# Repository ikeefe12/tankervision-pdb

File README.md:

# TankerVision Power Distribution Board

A four-layer KiCad power distribution board (PDB) for the TankerVision robot. It
accepts USB-C PD or an 18.5–20 V DC barrel-jack input, maintains a
supercapacitor-backed rail so an onboard NVIDIA Jetson can shut down cleanly after
input loss, and exposes four independently protected, firmware-controlled output
ports.

Designed in KiCad 9.0.7. Revision 1.0 was fabricated and assembled by JLCPCB in
August 2026.

| | |
|---|---|
|  |  |

## Highlights

- **Dual redundant input** — USB-C PD (CYPD3177 requesting 20 V) and a DC barrel
  jack are ORed through two reverse-blocking LM73100 ideal-diode switches.
- **Supercapacitor backup** — a BQ24640 charges an external bank through a 24.5 V
  LM5155 boost; a TPS2121 priority mux transfers the backed `+VBUS_SS` domain to the
  bank in roughly 5 µs when the input rail collapses.
- **Orderly shutdown** — the backed rails feed the ESP32-S3, which sheds loads,
  pulses the Jetson power button, and watches stored energy on the supercap ADC
  divider to decide when to commit to shutdown.
- **Firmware-independent boot** — input switch → mux IN1 → `+VBUS_SS` → 5 V buck →
  3.3 V LDO brings up the ESP32-S3 with no firmware involvement; every other load
  rail is deliberately under software control.
- **Protected outputs** — four LM73100 output switches provide inrush control,
  reverse blocking, power-good, and current monitoring per port.
- **Full supervision** — fourteen TLV7031 comparators condition status signals and
  two TCA9535 I²C expanders carry enables and status back to the ESP32-S3.

## Board summary

| Item | Value |
|---|---|
| Outline | 100 mm × 100 mm |
| Stackup | 4-layer, 1.6 mm FR-4, 35 µm (1 oz) copper on all layers |
| Planes | In1.Cu solid GND; In2.Cu predominantly GND with selected routing |
| References | 452 in schematic and PCB, matched one-to-one |
| Production BOM | 444 fitted references in 84 orderable groups |
| Input | USB-C PD, or 18.5–20 V DC barrel jack |
| Outputs | 4 protected ports (`+VBUS`, `+5V_VBUS`, `+VBUS_SS`, `+5V_SS`) |
| Controller | ESP32-S3-WROOM-1-N8R8 |

## Documentation

The design is documented per functional block, with schematic labels rather than
drawing coordinates used as the stable way to locate each circuit.

- **[docs/README.md](docs/README.md)** — start here: block index and power-rail table
- **[docs/system-architecture.md](docs/system-architecture.md)** — power flow, control
  and status map, ESP32 pin map, sequencing
- **[docs/pcb-layout.md](docs/pcb-layout.md)** — layout review, stackup, routing,
  fabrication decisions, revision-1.0 order record
- **[docs/issues.md](docs/issues.md)** — open design concerns and pre-deployment
  bench checks
- **[docs/blocks/](docs/blocks/)** — sixteen per-block documents covering USB-PD,
  inrush control, the power mux, the supercap charger and switch, the boost and
  bucks, LDOs, output switches, the ESP32, I/O expanders, comparators, analog
  switches, the Jetson power button, and ADC monitoring

Firmware and board verification:

- **[firmware/deployment/README.md](firmware/deployment/README.md)** — automatic
  startup, supercap maintenance charging, 1 Hz USB telemetry and fixed 60-second
  Jetson shutdown/reboot sequence
- **[firmware/deployment/API.md](firmware/deployment/API.md)** — Jetson USB API,
  with a [Python reference client](firmware/deployment/jetson/README.md)
- **[firmware/deployment/results/upload-2026-09-16/README.md](firmware/deployment/results/upload-2026-09-16/README.md)**
  — verified deployment upload, charging/PG observations and serial reopen results
- **[firmware/board_control_test/README.md](firmware/board_control_test/README.md)**
  — reusable board drivers, bench procedures and historical test results

Generated exports for quick reading without KiCad:

- [docs/exports/tankervision-pdb-schematic.pdf](docs/exports/tankervision-pdb-schematic.pdf)
- [docs/exports/tankervision-pdb-bom.csv](docs/exports/tankervision-pdb-bom.csv)

## Repository layout

```text
hardware/tankervision-pdb/   KiCad project (schematic, PCB, project library tables)
libraries/symbols/           custom symbol libraries (.kicad_sym)
libraries/footprints/        custom footprint libraries (.pretty)
libraries/3dmodels/          custom 3D models referenced by those footprints
docs/                        design documentation, generated exports and renders
firmware/deployment/         ESP32 deployment firmware, Jetson API/client and tests
firmware/board_control_test/  hardware bench firmware, procedures and captured results
manufacturing/rev-1_0/       as-ordered JLCPCB fabrication and assembly package
```

## Opening the project

Requires **KiCad 9.0** or newer.

```sh
git clone https://github.com/ikeefe12/tankervision-pdb.git
cd tankervision-pdb
kicad hardware/tankervision-pdb/tankervision-pdb.kicad_pro
```

The project's `sym-lib-table` and `fp-lib-table` resolve every custom library
through `${KIPRJMOD}/../../libraries/...`, so the libraries load from this
repository with no global KiCad configuration. Standard symbols, footprints, and 3D
models come from the stock KiCad libraries installed with KiCad.

## Design state

Revision 1.0 was ordered from JLCPCB on 2026-08-24. The CAD review finds no
remaining electrical schematic blocker. The firmware records now include successful
converter/port control checks, real-bank charging and backup intervals, and the
first deployment upload with 1 Hz telemetry and same-boot serial reopen on the Mac.
The remaining integration checks in [docs/issues.md](docs/issues.md) include loaded
Jetson shutdown and backup endurance, source hot-plug, thermal validation of the
3.3 V LDO, and output-switch overload cases. The recorded unloaded and MCU-only
checks do not establish those loaded behaviors.

Verification on the current sources with KiCad 9.0.7:

- PCB DRC with schematic parity: 0 violations, 0 unconnected pads, 0 footprint
  errors, 0 parity issues.
- ERC is clean in the KiCad GUI with the project's review exclusions applied.
  Command-line ERC does not apply those exclusions and reports six
  `power_pin_not_driven` items, all of which are the reviewed and accepted cases
  described in the block documentation.

## Credit

Designed by Ian Keefe at TRAILab, University of Toronto Institute for Aerospace
Studies.

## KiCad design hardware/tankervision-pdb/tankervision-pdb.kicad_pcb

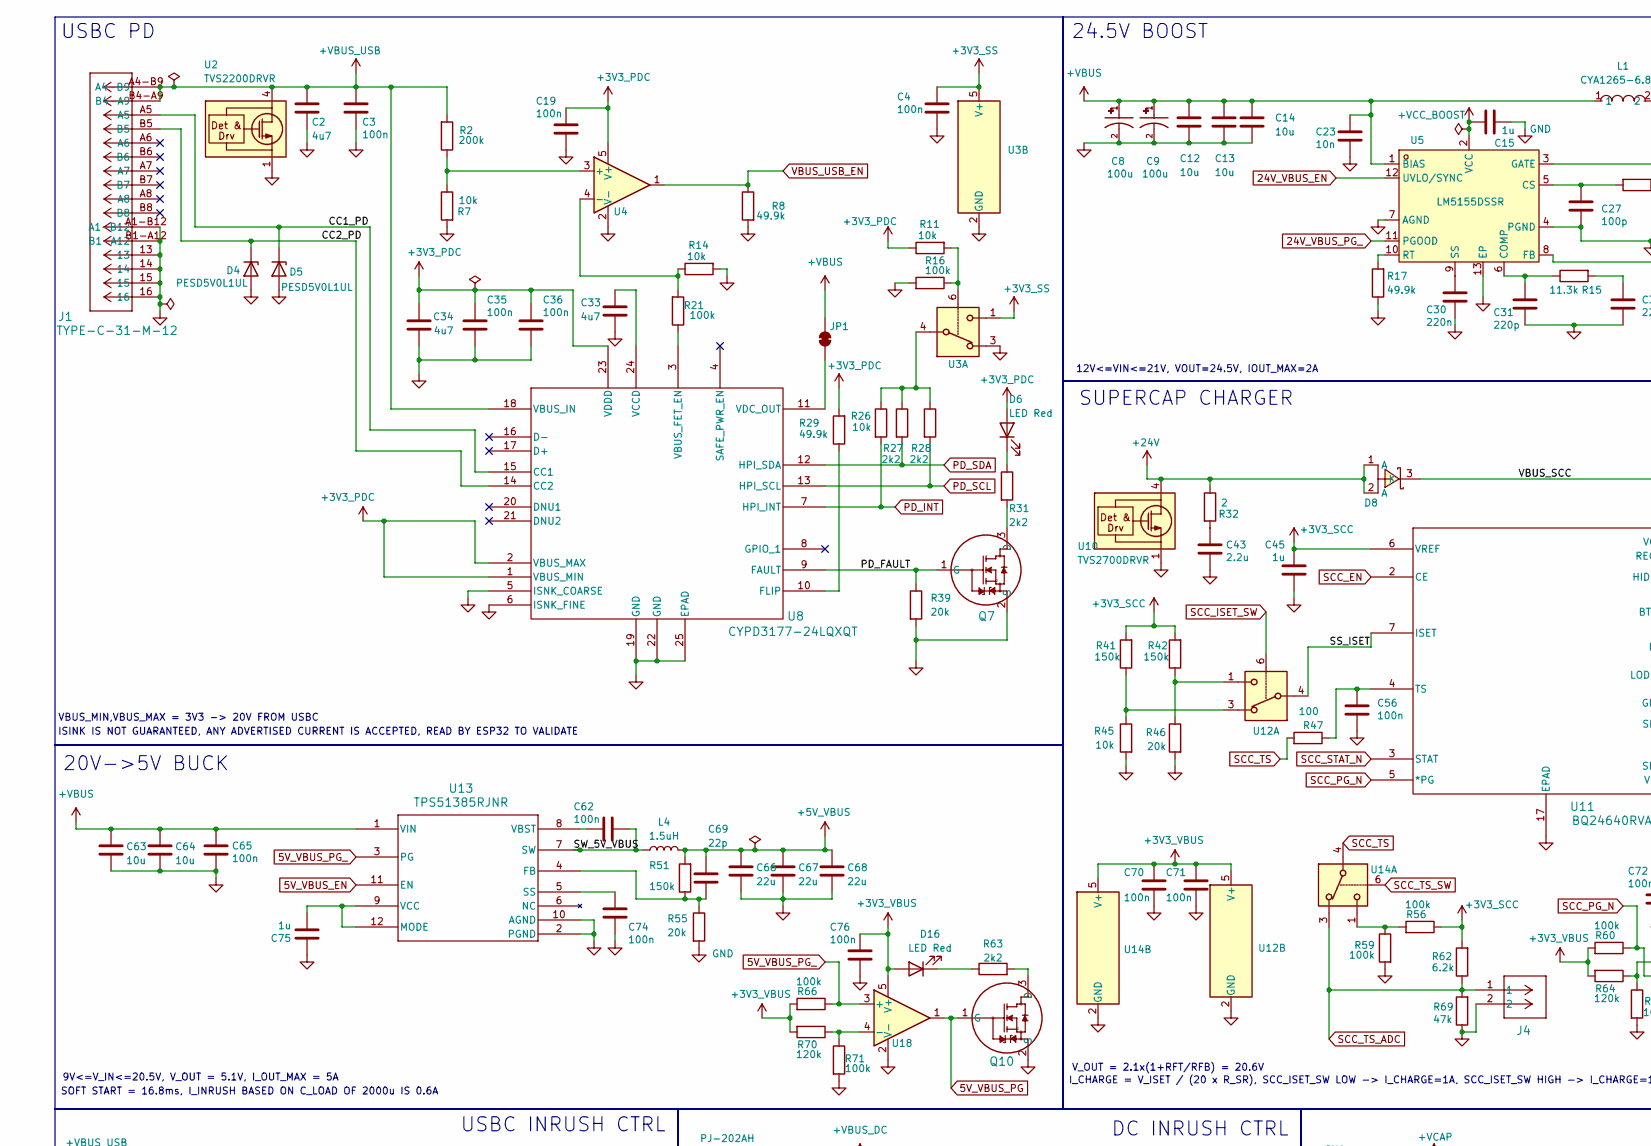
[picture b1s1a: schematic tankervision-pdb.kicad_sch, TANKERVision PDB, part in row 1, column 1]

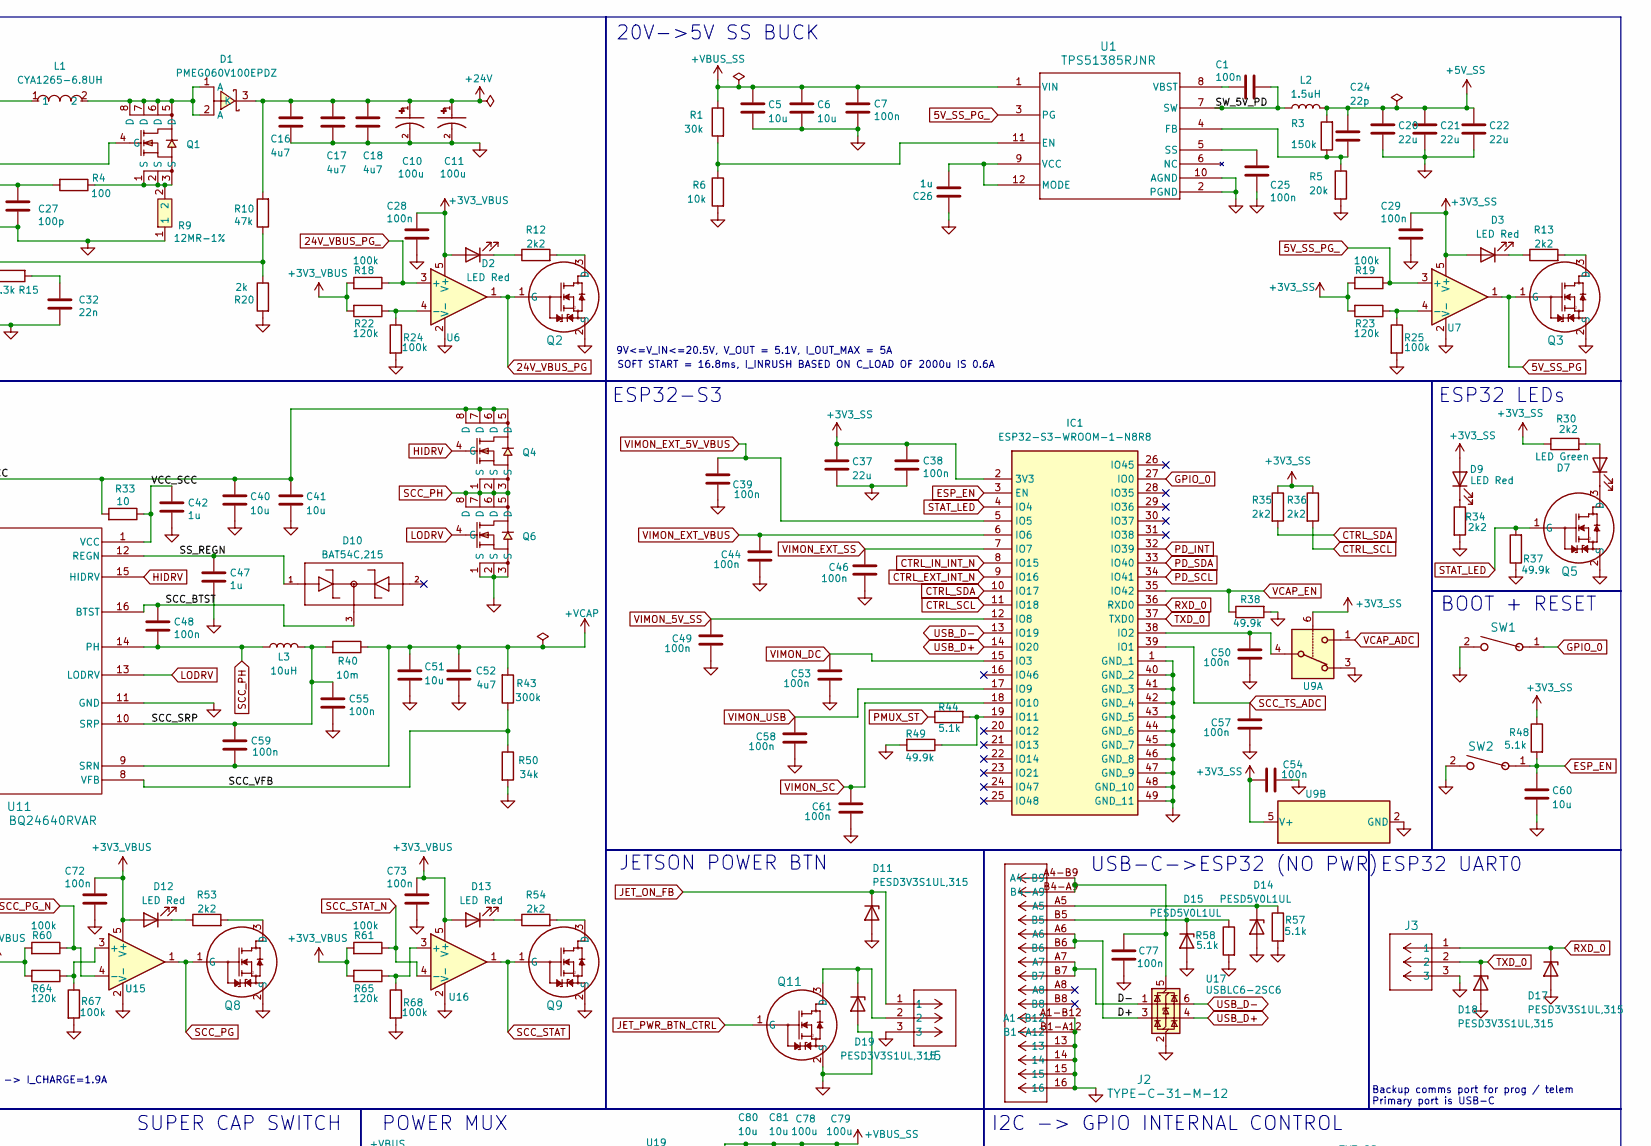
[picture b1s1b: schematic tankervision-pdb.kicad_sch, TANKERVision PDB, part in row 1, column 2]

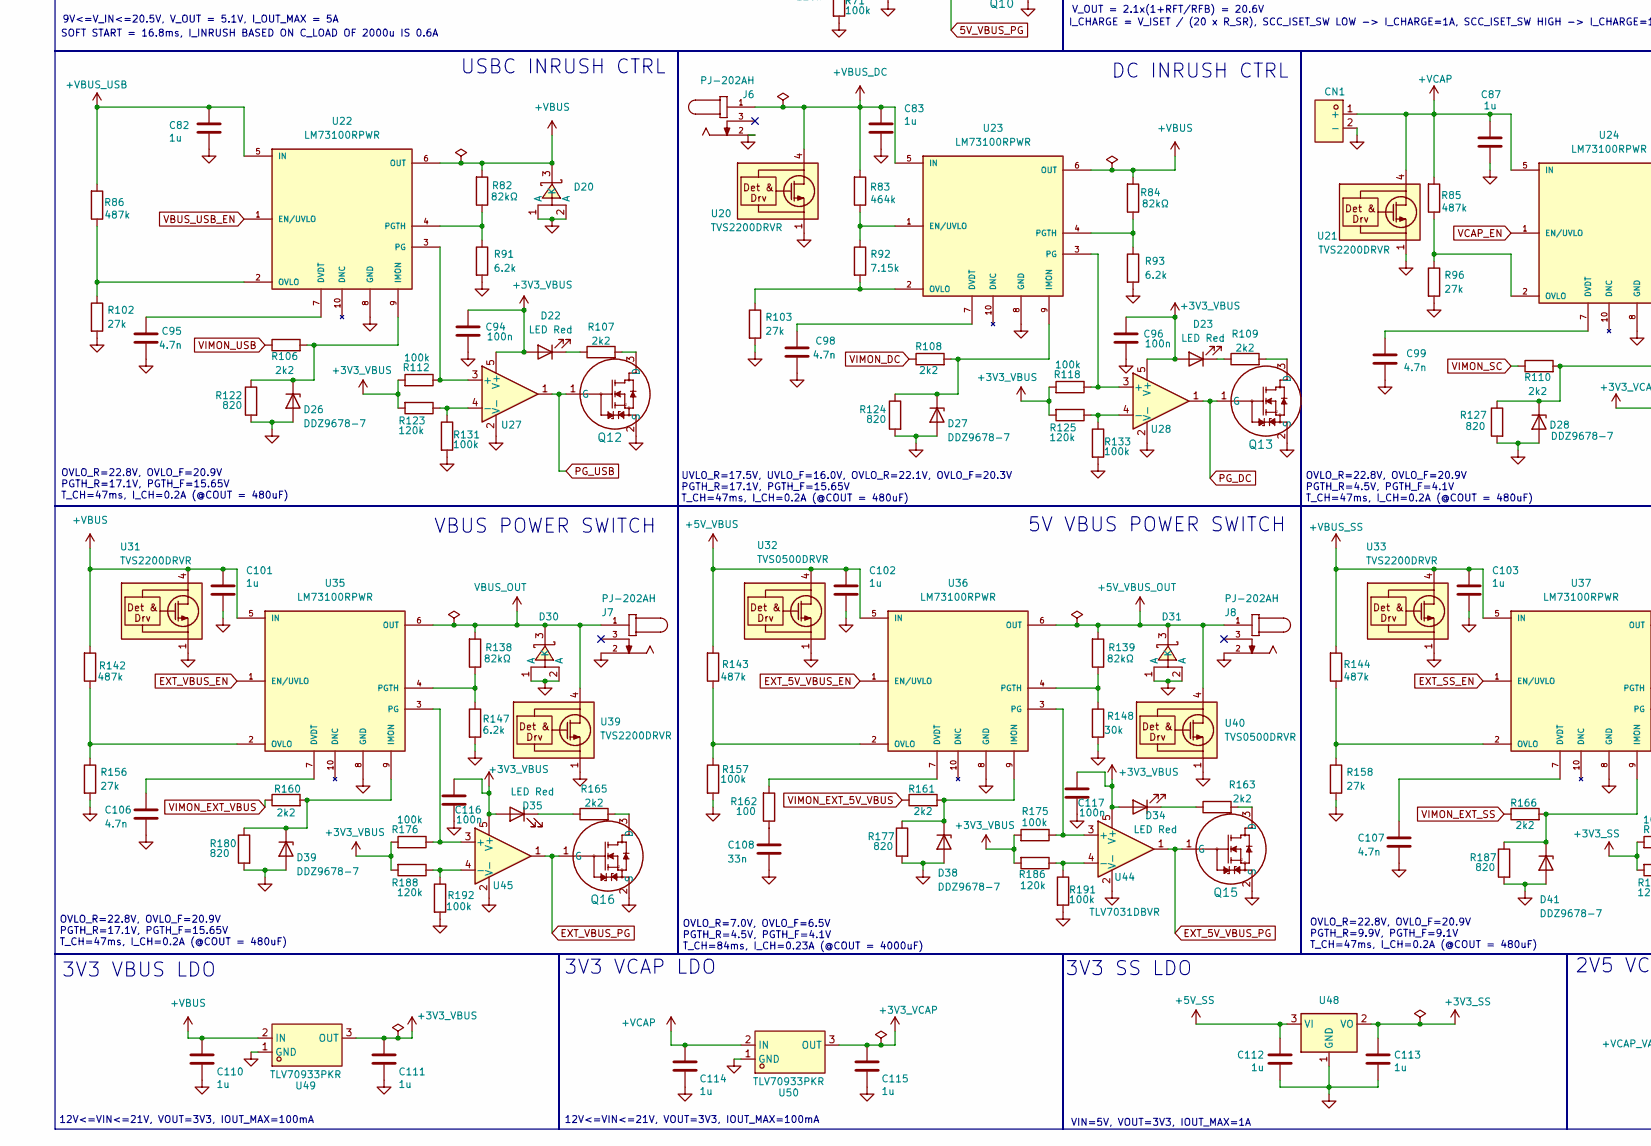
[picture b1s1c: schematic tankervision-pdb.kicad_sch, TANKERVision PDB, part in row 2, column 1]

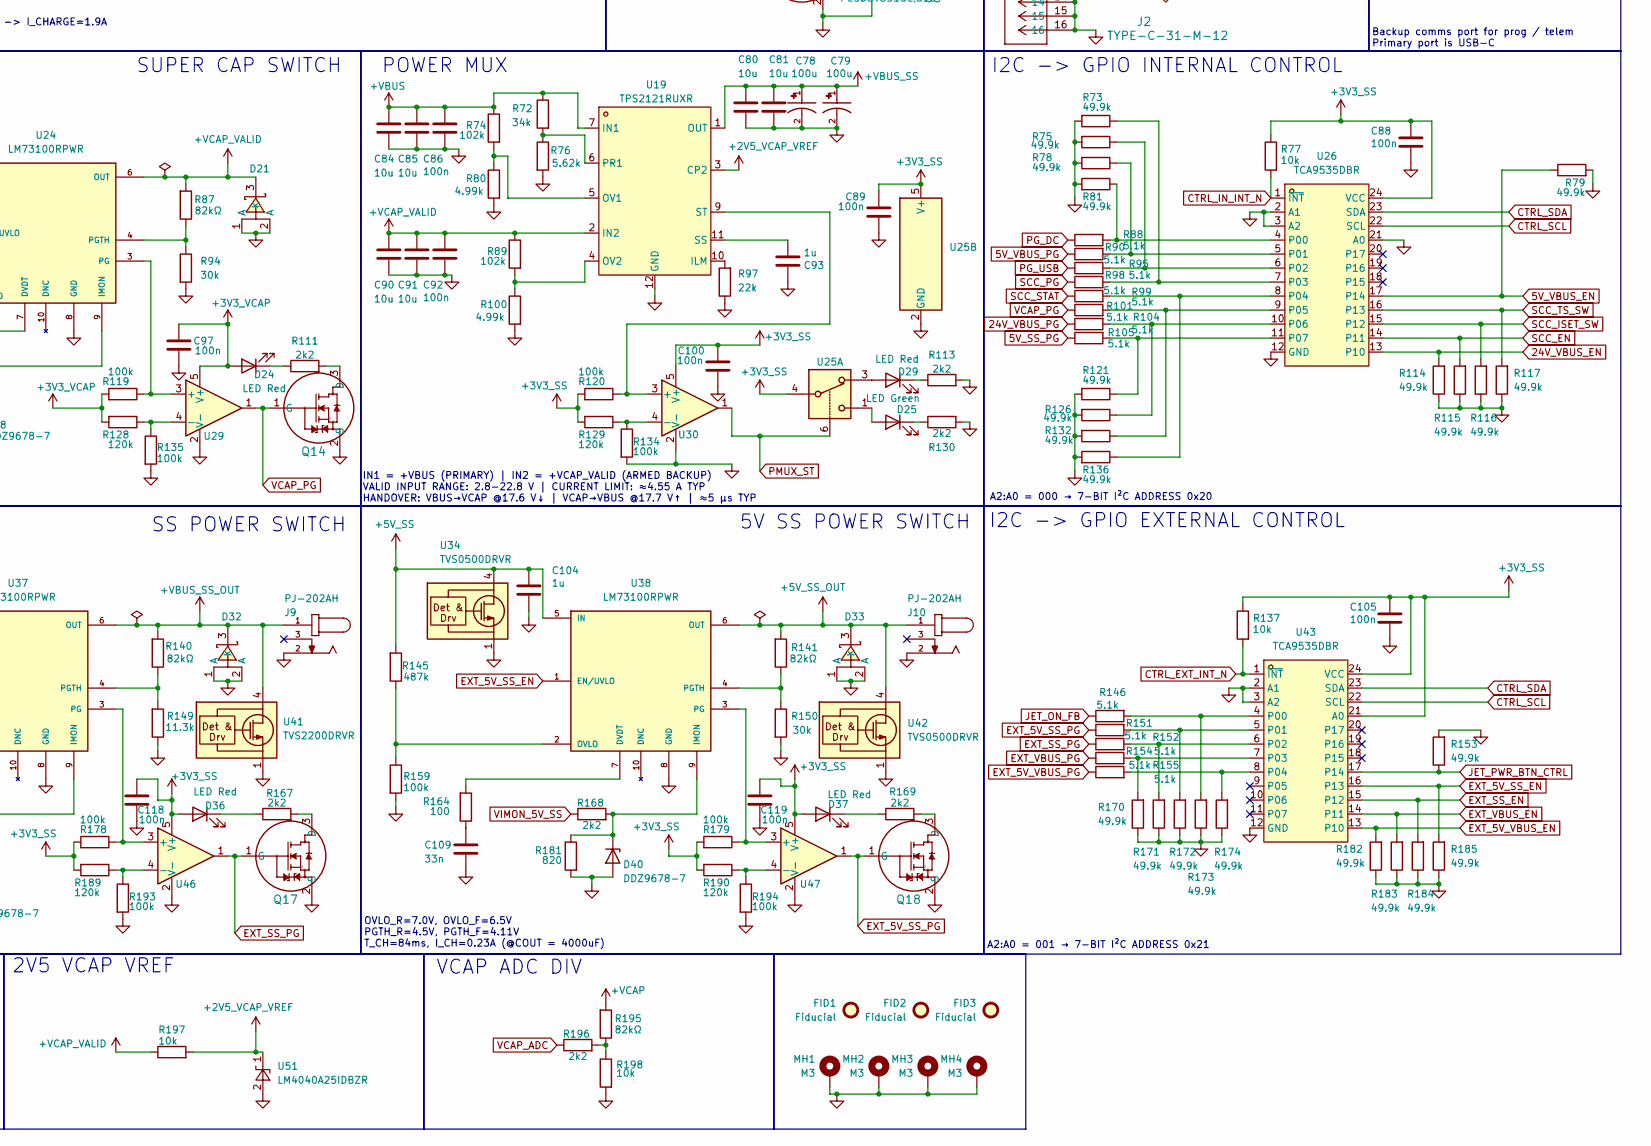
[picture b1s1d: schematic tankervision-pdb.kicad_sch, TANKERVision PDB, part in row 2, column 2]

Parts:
C1, C3, C4, C7, C19, C25, C28, C29, C35, C36, C38, C39, C44, C46, C48, C49, C50, C53, C54, C55, C56, C57, C58, C59, C61, C62, C65, C70, C71, C72, C73, C74, C76, C77, C86, C88, C89, C92, C94, C96, C97, C100, C105, C116, C117, C118, C119: 100n; C_0603_1608Metric; Manufacturer_Part_Number CC0603KRX7R9BB104; JLCPCB Part # C14663
C2, C16, C17, C18, C33, C34, C52: 4u7; C_1206_3216Metric; Manufacturer_Part_Number 1206B475K500NT; JLCPCB Part # C29823
C5, C6, C12, C13, C14, C40, C41, C51, C60, C63, C64, C80, C81, C84, C85, C90, C91: 10u; C_1206_3216Metric; Manufacturer_Part_Number CL31A106KBHNNNE; JLCPCB Part # C13585
C8, C9, C10, C11, C78, C79: 100u; CAP_EEHZA1H101V; Manufacturer_Part_Number EEHZA1H101V; JLCPCB Part # C454363
C15, C26, C42, C45, C47, C75, C82, C83, C87, C93, C101, C102, C103, C104, C110, C111, C112, C113, C114, C115: 1u; C_0805_2012Metric; Manufacturer_Part_Number CL21B105KBFNNNE; JLCPCB Part # C28323
C20, C21, C22, C37, C66, C67, C68: 22u; C_1206_3216Metric; Manufacturer_Part_Number CL31A226KAHNNNE; JLCPCB Part # C12891
C23: 10n; C_0603_1608Metric; Manufacturer_Part_Number 0603B103K500NT; JLCPCB Part # C57112
C24, C69: 22p; C_0603_1608Metric; Manufacturer_Part_Number CL10C220JB8NNNC; JLCPCB Part # C1653
C27: 100p; C_0603_1608Metric; Manufacturer_Part_Number 0603CG101F500NT; JLCPCB Part # C55722
C30: 220n; C_0603_1608Metric; Manufacturer_Part_Number CL10B224KA8NNNC; JLCPCB Part # C21120
C31: 220p; C_0603_1608Metric; Manufacturer_Part_Number GCM1885C2A221JA16D; JLCPCB Part # C388907
C32: 22n; C_0603_1608Metric; Manufacturer_Part_Number CL10B223KB8NNNC; JLCPCB Part # C21122
C43: 2.2u; C_1206_3216Metric; Manufacturer_Part_Number CL31B225KBHNNNE; JLCPCB Part # C50254
C95, C98, C99, C106, C107: 4.7n; C_0805_2012Metric_Pad1.18x1.45mm_HandSolder; Manufacturer_Part_Number 0805B472K500NT; JLCPCB Part # C1744
C108, C109: 33n; C_0805_2012Metric_Pad1.18x1.45mm_HandSolder; Manufacturer_Part_Number 0805B333K500NT; JLCPCB Part # C1739
CN1: XT30APW-M; CONN-TH_XT30APW-M; Manufacturer_Part_Number XT30APW-M; JLCPCB Part # C5818955
D1, D8, D20, D21, D30, D31, D32, D33: PMEG060V100EPDZ; SOT1289_L5.8-W4.4-LS6.5-RD; Manufacturer_Part_Number PMEG060V100EPDZ; JLCPCB Part # C552792
D2, D3, D6, D9, D12, D13, D16, D22, D23, D24, D29, D34, D35, D36, D37: LED Red; LED_0805_2012Metric; Manufacturer_Part_Number XL-2012SURC-FJ; JLCPCB Part # C7371909
D4, D5, D14, D15: PESD5V0L1UL; D_SOD-882; Manufacturer_Part_Number PESD5V0L1UL; JLCPCB Part # C3001948
D7, D25: LED Green; LED_0805_2012Metric; Manufacturer_Part_Number XL-2012UGC; JLCPCB Part # C965815
D10: BAT54C,215; SOT-23; Manufacturer_Part_Number BAT54C,215; JLCPCB Part # C37704
D11, D17, D18, D19: PESD3V3S1UL,315; D_SOD-882; Manufacturer_Part_Number PESD3V3S1UL,315; JLCPCB Part # C70371
D26, D27, D28, D38, D39, D40, D41: DDZ9678-7; D_SOD-123; Manufacturer_Part_Number DDZ9678-7; JLCPCB Part # C150464
FID1, FID2, FID3: Fiducial; Fiducial_1mm_Mask2mm
IC1: ESP32-S3-WROOM-1-N8R8; ESP32S3WROOM1N8R8; Manufacturer_Part_Number ESP32-S3-WROOM-1-N8R8; JLCPCB Part # C2913201
J1, J2: TYPE-C-31-M-12; CONN12_C-31-M-12_HRO; Manufacturer_Part_Number TYPE-C-31-M-12; JLCPCB Part # C165948
J3, J5: S3B-PH-K-S LFSN; CONN_S3B-PH-K-S_JST; Manufacturer_Part_Number S3B-PH-K-S(LF)(SN); JLCPCB Part # C157929
J4: S2B-PH-K-SLFSN; CONN_S2B-PH-K-S_JST; Manufacturer_Part_Number S2B-PH-K-S(LF)(SN); JLCPCB Part # C173752
J6, J7, J8, J9, J10: PJ-202AH; CUI_PJ-202AH; Manufacturer_Part_Number PJ-202AH; JLCPCB Part # C7435395
JP1: SolderJumper_2_Bridged; SolderJumper-2_P1.3mm_Bridged_RoundedPad1.0x1.5mm
L1: CYA1265-6.8UH; IND-SMD_L12.8-W12.8-LS13.8_CYA1265; Manufacturer_Part_Number CYA1265-6.8UH; JLCPCB Part # C19268667
L2, L4: 1.5uH; IND_MWSA0603S_SNL-M; Manufacturer_Part_Number MWSA0603S-1R5MT; JLCPCB Part # C408444
L3: 10uH; SMDRI127100MT; Manufacturer_Part_Number SMDRI127-100MT; JLCPCB Part # C9904
MH1, MH2, MH3, MH4: M3; MountingHole_3.2mm_M3_Pad_Via
Q1, Q4, Q6: IPC50N04S5L5R5ATMA1; PG-TDSON-8-FL_L5.0-W6.0-P1.27-LS6.2-BL; Manufacturer_Part_Number IPC50N04S5L5R5ATMA1; JLCPCB Part # C3288870
Q2, Q3, Q5, Q7, Q8, Q9, Q10, Q11, Q12, Q13, Q14, Q15, Q16, Q17, Q18: 2N7002NXAKR; TO-236AB_SOT23_NEX-M; Manufacturer_Part_Number 2N7002NXAKR; JLCPCB Part # C551416
R1, R94, R148, R150: 30k; R_0603_1608Metric; Manufacturer_Part_Number 0603WAF3002T5E; JLCPCB Part # C22984
R2: 200k; R_0603_1608Metric; Manufacturer_Part_Number 0603WAF2003T5E; JLCPCB Part # C25811
R3, R41, R42, R51: 150k; R_0603_1608Metric; Manufacturer_Part_Number 0603WAF1503T5E; JLCPCB Part # C22807
R4, R47, R162, R164: 100; R_0603_1608Metric; Manufacturer_Part_Number 0603WAF1000T5E; JLCPCB Part # C22775
R5, R39, R55: 20k; R_0603_1608Metric; Manufacturer_Part_Number 0603WAF2002T5E; JLCPCB Part # C4184
R6, R7, R11, R14, R26, R77, R137, R197, R198: 10k; R_0603_1608Metric; Manufacturer_Part_Number 0603WAF1002T5E; JLCPCB Part # C25804
R8, R17, R29, R37, R38, R49, R73, R75, R78, R79, R81, R114, R115, R116, R117, R121, R126, R132, R136, R153, R170, R171, R172, R173, R174, R182, R183, R184, R185: 49.9k; R_0603_1608Metric; Manufacturer_Part_Number 0603WAF4992T5E; JLCPCB Part # C23184
R9: 12MR-1%; RES-SMD_L6.4-W3.2_LR2512D-3W-1MR; Manufacturer_Part_Number HoLLR2512-2W-12mR-1%; JLCPCB Part # C2994622
R10, R69: 47k; R_0805_2012Metric_Pad1.20x1.40mm_HandSolder; Manufacturer_Part_Number RT0805BRE0747KL; JLCPCB Part # C866080
R12, R13, R27, R28, R30, R31, R34, R35, R36, R53, R54, R63, R106, R107, R108, R109, R110, R111, R113, R130, R160, R161, R163, R165, R166, R167, R168, R169, R196: 2k2; R_0603_1608Metric; Manufacturer_Part_Number 0603WAF2201T5E; JLCPCB Part # C4190
R15, R149: 11.3k; R_0603_1608Metric; Manufacturer_Part_Number 0603WAF1132T5E; JLCPCB Part # C22860
R16, R18, R19, R21, R24, R25, R56, R59, R60, R61, R66, R67, R68, R71, R112, R118, R119, R120, R131, R133, R134, R135, R157, R159, R175, R176, R178, R179, R191, R192, R193, R194: 100k; R_0603_1608Metric; Manufacturer_Part_Number 0603WAF1003T5E; JLCPCB Part # C25803
R20: 2k; R_0805_2012Metric_Pad1.20x1.40mm_HandSolder; Manufacturer_Part_Number 0805W8F2001T5E; JLCPCB Part # C17604
R22, R23, R64, R65, R70, R123, R125, R128, R129, R186, R188, R189, R190: 120k; R_0603_1608Metric; Manufacturer_Part_Number 0603WAF1203T5E; JLCPCB Part # C25808
R32: 2; R_0603_1608Metric; Manufacturer_Part_Number 0603WAF200KT5E; JLCPCB Part # C22977
R33: 10; R_0603_1608Metric; Manufacturer_Part_Number 0603WAF100JT5E; JLCPCB Part # C22859
R40: 10m; R_2512_6332Metric; Manufacturer_Part_Number PCSR2512DR010M6; JLCPCB Part # C7470248
R43: 300k; R_0805_2012Metric_Pad1.20x1.40mm_HandSolder; Manufacturer_Part_Number RT0805BRD07300KL; JLCPCB Part # C865386
R44, R48, R57, R58, R88, R90, R95, R98, R99, R101, R104, R105, R146, R151, R152, R154, R155: 5.1k; R_0603_1608Metric; Manufacturer_Part_Number 0603WAF5101T5E; JLCPCB Part # C23186
R45: 10k; R_0805_2012Metric_Pad1.20x1.40mm_HandSolder; Manufacturer_Part_Number 0805W8F1002T5E; JLCPCB Part # C17414
R46: 20k; R_0805_2012Metric_Pad1.20x1.40mm_HandSolder; Manufacturer_Part_Number 0805W8F2002T5E; JLCPCB Part # C4328
R50, R72: 34k; R_0805_2012Metric_Pad1.20x1.40mm_HandSolder; Manufacturer_Part_Number RT0805BRD0734KL; JLCPCB Part # C865418
R62: 6.2k; R_0805_2012Metric_Pad1.20x1.40mm_HandSolder; Manufacturer_Part_Number RT0805BRD076K2L; JLCPCB Part # C326695
R74, R89: 102k; R_0805_2012Metric_Pad1.20x1.40mm_HandSolder; Manufacturer_Part_Number RT0805BRD07102KL; JLCPCB Part # C865126
R76: 5.62k; R_0805_2012Metric_Pad1.20x1.40mm_HandSolder; Manufacturer_Part_Number RT0805BRD075K62L; JLCPCB Part # C706248
R80, R100: 4.99k; R_0805_2012Metric_Pad1.20x1.40mm_HandSolder; Manufacturer_Part_Number RT0805BRD074K99L; JLCPCB Part # C706246
R82, R84, R87, R138, R139, R140, R141, R195: 82kΩ; R_0805_2012Metric_Pad1.20x1.40mm_HandSolder; Manufacturer_Part_Number 0805W8F8202T5E; JLCPCB Part # C17840
R83: 464k; R_0805_2012Metric_Pad1.20x1.40mm_HandSolder; Manufacturer_Part_Number 0805W8F4643T5E; JLCPCB Part # C17706
R85, R86, R142, R143, R144, R145: 487k; R_0805_2012Metric_Pad1.20x1.40mm_HandSolder; Manufacturer_Part_Number 0805W8F4873T5E; JLCPCB Part # C17717
R91, R93, R147: 6.2k; R_0603_1608Metric; Manufacturer_Part_Number 0603WAF6201T5E; JLCPCB Part # C4260
R92: 7.15k; R_0805_2012Metric_Pad1.20x1.40mm_HandSolder; Manufacturer_Part_Number 0805W8F7151T5E; JLCPCB Part # C17806
R96, R102, R103, R156, R158: 27k; R_0805_2012Metric_Pad1.20x1.40mm_HandSolder; Manufacturer_Part_Number 0805W8F2702T5E; JLCPCB Part # C17593
R97: 22k; R_0603_1608Metric; Manufacturer_Part_Number 0603WAF2202T5E; JLCPCB Part # C31850
R122, R124, R127, R177, R180, R181, R187: 820; R_0603_1608Metric; Manufacturer_Part_Number 0603WAF8200T5E; JLCPCB Part # C23253
SW1, SW2: TS-1088-AR02016; SW_TS-1088_XNP-M; Manufacturer_Part_Number TS-1088-AR02016; JLCPCB Part # C720477
U1, U13: TPS51385RJNR; VQFN-HR12_RJN_TEX; Manufacturer_Part_Number TPS51385RJNR; JLCPCB Part # C22418767
U2, U20, U21, U31, U33, U39, U41: TVS2200DRVR; WSON-6-1EP_2x2mm_P0.65mm_EP1x1.6mm; Manufacturer_Part_Number TVS2200DRVR; JLCPCB Part # C523793
U3, U9, U12, U14, U25: TS5A3159ADBVR; SOT-23-6; Manufacturer_Part_Number TS5A3159ADBVR; JLCPCB Part # C128405
U4, U6, U7, U15, U16, U18, U27, U28, U29, U30, U44, U45, U46, U47: TLV7031DBVR; SOT-23-5; Manufacturer_Part_Number TLV7031DBVR; JLCPCB Part # C2869832
U5: LM5155DSSR; WSON-12_L3.0-W2.0-P0.50-BL-EP; Manufacturer_Part_Number LM5155DSSR; JLCPCB Part # C545416
U8: CYPD3177-24LQXQT; QFN24_CYPD3177-24LQXQT_INF; Manufacturer_Part_Number CYPD3177-24LQXQT; JLCPCB Part # C2952489
U10: TVS2700DRVR; WSON-6-1EP_2x2mm_P0.65mm_EP1x1.6mm; Manufacturer_Part_Number TVS2700DRVR; JLCPCB Part # C523797
U11: BQ24640RVAR; RVA16_2P14X2P14; Manufacturer_Part_Number BQ24640RVAR; JLCPCB Part # C545157
U17: USBLC6-2SC6; SOT-23-6; Manufacturer_Part_Number USBLC6-2SC6; JLCPCB Part # C7519
U19: TPS2121RUXR; VQFN-HR-12_L2.5-W2.0-P0.50-BL; Manufacturer_Part_Number TPS2121RUXR; JLCPCB Part # C485916
U22, U23, U24, U35, U36, U37, U38: LM73100RPWR; IC_LM73100RPWR; Manufacturer_Part_Number LM73100RPWR; JLCPCB Part # C3210761
U26, U43: TCA9535DBR; SSOP-24_L8.1-W5.3-P0.65-LS7.8-BL; Manufacturer_Part_Number TCA9535DBR; JLCPCB Part # C2652322
U32, U34, U40, U42: TVS0500DRVR; WSON-6-1EP_2x2mm_P0.65mm_EP1x1.6mm; Manufacturer_Part_Number TVS0500DRVR; JLCPCB Part # C609571
U48: TLV1117LV33DCYR; SOT-223-3_TabPin2; Manufacturer_Part_Number TLV1117LV33DCYR; JLCPCB Part # C15578
U49, U50: TLV70933PKR; SOT-89-3_L4.3-W2.3-P1.50-LS4.3-BR; Manufacturer_Part_Number TLV70933PKR; JLCPCB Part # C22445454
U51: LM4040A25IDBZR; SOT-23; Manufacturer_Part_Number LM4040A25IDBZR; JLCPCB Part # C9421

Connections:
5V_SS_PG: Q3.1 (G), R105.1, U7.1
5V_SS_PG_: R19.1, U1.3 (PG), U7.3 (+)
5V_VBUS_EN: R79.1, U13.11 (EN), U26.17 (P14)
5V_VBUS_PG: Q10.1 (G), R90.1, U18.1
5V_VBUS_PG_: R66.1, U13.3 (PG), U18.3 (+)
24V_VBUS_EN: R114.2, U5.12 (UVLO/SYNC), U26.13 (P10)
24V_VBUS_PG: Q2.1 (G), R104.1, U6.1
24V_VBUS_PG_: R18.1, U5.11 (PGOOD), U6.3 (+)
+2V5_VCAP_VREF: R197.2, U19.3 (CP2), U51.1 (K)
+3V3_PDC: C19.2, C34.1, C35.1, C36.1, D6.2 (A), R11.1, R29.2, U4.5 (V+), U8.1 (VBUS_MIN), U8.2 (VBUS_MAX), U8.23 (VDDD)
+3V3_SCC: C45.1, R41.2, R42.2, R56.1, R62.2, U11.6 (VREF)
+3V3_SS: C4.1, C29.2, C37.2, C38.1, C54.1, C88.1, C89.1, C100.1, C105.1, C113.1, C118.1, C119.1, D3.2 (A), D9.2 (A), D36.2 (A), D37.2 (A), IC1.2 (3V3), R19.2, R23.2, R30.1, R35.1, R36.1, R48.1, R77.1, R120.2, R129.2, R137.1, R178.2, R179.2, R189.2, R190.2, U3.1, U3.5 (V+), U7.5 (V+), U9.5 (V+), U9.6, U25.4, U25.5 (V+), U26.24 (VCC), U30.5 (V+), U43.21 (A0), U43.24 (VCC), U46.5 (V+), U47.5 (V+), U48.2 (VO)
+3V3_VBUS: C28.2, C70.2, C71.2, C72.2, C73.2, C76.2, C94.1, C96.1, C111.1, C116.1, C117.1, D2.2 (A), D12.2 (A), D13.2 (A), D16.2 (A), D22.2 (A), D23.2 (A), D34.2 (A), D35.2 (A), R18.2, R22.2, R60.2, R61.2, R64.2, R65.2, R66.2, R70.2, R112.2, R118.2, R123.2, R125.2, R175.2, R176.2, R186.2, R188.2, U6.5 (V+), U12.5 (V+), U14.5 (V+), U15.5 (V+), U16.5 (V+), U18.5 (V+), U27.5 (V+), U28.5 (V+), U44.5 (V+), U45.5 (V+), U49.3 (OUT)
+3V3_VCAP: C97.1, C115.1, D24.2 (A), R119.2, R128.2, U29.5 (V+), U50.3 (OUT)
+5V_SS: C20.2, C21.2, C22.2, C24.2, C104.1, C112.1, L2.2, R3.2, R145.2, U34.4 (IN), U34.5 (IN), U34.6 (IN), U38.5 (IN), U48.3 (VI)
+5V_SS_OUT: D33.3 (K), J10.1, R141.2, U38.6 (OUT), U42.4 (IN), U42.5 (IN), U42.6 (IN)
+5V_VBUS: C66.2, C67.2, C68.2, C69.2, C102.1, L4.2, R51.2, R143.2, U32.4 (IN), U32.5 (IN), U32.6 (IN), U36.5 (IN)
+5V_VBUS_OUT: D31.3 (K), J8.1, R139.2, U36.6 (OUT), U40.4 (IN), U40.5 (IN), U40.6 (IN)
+24V: C10.1, C11.1, C16.1, C17.1, C18.1, D1.3 (K), D8.1 (A), D8.2 (A), R10.2, R32.1, U10.4 (IN), U10.5 (IN), U10.6 (IN)
+VBUS: C8.1, C9.1, C12.2, C13.2, C14.2, C23.1, C63.2, C64.2, C65.1, C84.2, C85.2, C86.1, C101.1, C110.1, D20.3 (K), JP1.2 (B), L1.1, R72.1, R74.1, R82.2, R84.2, R142.2, U5.1 (BIAS), U13.1 (VIN), U19.7 (IN1), U22.6 (OUT), U23.6 (OUT), U31.4 (IN), U31.5 (IN), U31.6 (IN), U35.5 (IN), U49.2 (IN)
+VBUS_DC: C83.1, J6.1, R83.2, U20.4 (IN), U20.5 (IN), U20.6 (IN), U23.5 (IN)
+VBUS_SS: C5.2, C6.2, C7.1, C78.1, C79.1, C80.2, C81.2, C103.1, R1.1, R144.2, U1.1 (VIN), U19.1 (OUT), U19.8 (OUT), U33.4 (IN), U33.5 (IN), U33.6 (IN), U37.5 (IN)
+VBUS_SS_OUT: D32.3 (K), J9.1, R140.2, U37.6 (OUT), U41.4 (IN), U41.5 (IN), U41.6 (IN)
+VBUS_USB: C2.1, C3.1, C82.1, J1.A4-B9, J1.B4-A9, R2.2, R86.2, U2.4 (IN), U2.5 (IN), U2.6 (IN), U8.18 (VBUS_IN), U22.5 (IN)
+VCAP: C51.2, C52.1, C59.2, C87.1, C114.1, CN1.1 (+), R40.1, R43.2, R85.2, R195.2, U11.9 (SRN), U21.4 (IN), U21.5 (IN), U21.6 (IN), U24.5 (IN), U50.2 (IN)
+VCAP_VALID: C90.2, C91.2, C92.1, D21.3 (K), R87.2, R89.1, R197.1, U19.2 (IN2), U24.6 (OUT)
+VCC_BOOST: C15.2, U5.2 (VCC)
/CC1_PD: D5.1 (K), J1.A5, U8.15 (CC1)
/CC2_PD: D4.1 (K), J1.B5, U8.14 (CC2)
/D+: J2.A6, J2.B6, U17.3 (I/O2)
/D-: J2.A7, J2.B7, U17.1 (I/O1)
/PD_FAULT: Q7.1 (G), R39.1, U8.9 (FAULT)
/SCC_BTST: C48.1, D10.3, U11.16 (BTST)
/SCC_SRP: C55.1, C59.1, L3.2, R40.2, U11.10 (SRP)
/SCC_VFB: R43.1, R50.1, U11.8 (VFB)
/SS_ISET: U11.7 (ISET), U12.4
/SS_REGN: C47.1, D10.1, U11.12 (REGN)
/SW_5V_PD: C1.2, L2.1, U1.7 (SW)
/SW_5V_VBUS: C62.2, L4.1, U13.7 (SW)
/VBUS_SCC: C40.2, C41.2, D8.3 (K), Q4.5 (D), Q4.6 (D), Q4.7 (D), Q4.8 (D), R33.2
/VCC_SCC: C42.1, R33.1, U11.1 (VCC)
CTRL_EXT_INT_N: IC1.9 (IO16), R137.2, U43.1 (~INT)
CTRL_IN_INT_N: IC1.8 (IO15), R77.2, U26.1 (~INT)
CTRL_SCL: IC1.11 (IO18), R36.2, U26.22 (SCL), U43.22 (SCL)
CTRL_SDA: IC1.10 (IO17), R35.2, U26.23 (SDA), U43.23 (SDA)
ESP_EN: C60.2, IC1.3 (EN), R48.2, SW2.1
EXT_5V_SS_EN: R185.2, U38.1 (EN/UVLO), U43.16 (P13)
EXT_5V_SS_PG: Q18.1 (G), R151.1, U47.1
EXT_5V_VBUS_EN: R182.2, U36.1 (EN/UVLO), U43.13 (P10)
EXT_5V_VBUS_PG: Q15.1 (G), R155.1, U44.1
EXT_SS_EN: R184.2, U37.1 (EN/UVLO), U43.15 (P12)
EXT_SS_PG: Q17.1 (G), R152.1, U46.1
EXT_VBUS_EN: R183.2, U35.1 (EN/UVLO), U43.14 (P11)
EXT_VBUS_PG: Q16.1 (G), R154.1, U45.1
GND: C2.2, C3.2, C4.2, C5.1, C6.1, C7.2, C8.2, C9.2, C10.2, C11.2, C12.1, C13.1, C14.1, C15.1, C16.2, C17.2, C18.2, C19.1, C20.1, C21.1, C22.1, C23.2, C25.2, C26.1, C27.2, C28.1, C29.1, C30.2, C31.2, C32.2, C33.2, C34.2, C35.2, C36.2, C37.1, C38.2, C39.2, C40.1, C41.1, C42.2, C43.2, C44.2, C45.2, C46.2, C47.2, C49.2, C50.2, C51.1, C52.2, C53.2, C54.2, C55.2, C56.2, C57.2, C58.2, C60.1, C61.2, C63.1, C64.1, C65.2, C66.1, C67.1, C68.1, C70.1, C71.1, C72.1, C73.1, C74.2, C75.1, C76.1, C77.2, C78.2, C79.2, C80.1, C81.1, C82.2, C83.2, C84.1, C85.1, C86.2, C87.2, C88.2, C89.2, C90.1, C91.1, C92.2, C93.1, C94.2, C95.1, C96.2, C97.2, C98.1, C99.1, C100.2, C101.2, C102.2, C103.2, C104.2, C105.2, C106.1, C107.1, C108.1, C109.1, C110.2, C111.2, C112.2, C113.2, C114.2, C115.2, C116.2, C117.2, C118.2, C119.2, CN1.2 (-), D4.2 (A), D5.2 (A), D11.2 (A), D14.2 (A), D15.2 (A), D17.2 (A), D18.2 (A), D19.2 (A), D20.1 (A), D20.2 (A), D21.1 (A), D21.2 (A), D26.2 (A), D27.2 (A), D28.2 (A), D30.1 (A), D30.2 (A), D31.1 (A), D31.2 (A), D32.1 (A), D32.2 (A), D33.1 (A), D33.2 (A), D38.2 (A), D39.2 (A), D40.2 (A), D41.2 (A), IC1.1 (GND_1), IC1.40 (GND_2), IC1.41 (GND_3), IC1.42 (GND_4), IC1.43 (GND_5), IC1.44 (GND_6), IC1.45 (GND_7), IC1.46 (GND_8), IC1.47 (GND_9), IC1.48 (GND_10), IC1.49 (GND_11), J1.13, J1.14, J1.15, J1.16, J1.A1-B12, J1.B1-A12, J2.13, J2.14, J2.15, J2.16, J2.A1-B12, J2.B1-A12, J3.3, J4.2, J5.3, J6.2, J7.2, J8.2, J9.2, J10.2, MH1.1, MH2.1, MH3.1, MH4.1, Q2.2 (S), Q3.2 (S), Q5.2 (S), Q6.1 (S), Q6.2 (S), Q6.3 (S), Q7.2 (S), Q8.2 (S), Q9.2 (S), Q10.2 (S), Q11.2 (S), Q12.2 (S), Q13.2 (S), Q14.2 (S), Q15.2 (S), Q16.2 (S), Q17.2 (S), Q18.2 (S), R5.2, R6.2, R7.2, R8.2, R9.1, R14.2, R16.2, R17.1, R20.2, R24.2, R25.2, R34.2, R37.1, R38.2, R39.2, R45.2, R46.2, R49.2, R50.2, R55.2, R57.2, R58.2, R59.2, R67.2, R68.2, R69.1, R71.2, R73.2, R75.2, R76.2, R78.2, R79.2, R80.2, R81.2, R91.2, R93.2, R94.2, R96.2, R97.1, R100.2, R102.2, R103.2, R113.2, R114.1, R115.1, R116.1, R117.1, R121.2, R122.2, R124.2, R126.2, R127.2, R130.2, R131.2, R132.2, R133.2, R134.2, R135.2, R136.2, R147.2, R148.2, R149.1, R150.2, R153.2, R156.2, R157.2, R158.2, R159.2, R170.1, R171.1, R172.1, R173.1, R174.1, R177.2, R180.2, R181.2, R182.1, R183.1, R184.1, R185.1, R187.2, R191.2, R192.2, R193.2, R194.2, R198.2, SW1.2, SW2.2, U1.2 (PGND), U1.10 (AGND), U2.1 (GND), U2.2 (GND), U2.3 (GND), U2.7 (GND), U3.2 (GND), U3.3, U4.2 (V-), U5.4 (PGND), U5.7 (AGND), U5.13 (EP), U6.2 (V-), U7.2 (V-), U8.5 (ISNK_COARSE), U8.6 (ISNK_FINE), U8.19 (GND), U8.22 (GND), U8.25 (EPAD), U9.2 (GND), U9.3, U10.1 (GND), U10.2 (GND), U10.3 (GND), U10.7 (GND), U11.11 (GND), U11.17 (EPAD), U12.2 (GND), U13.2 (PGND), U13.10 (AGND), U14.2 (GND), U15.2 (V-), U16.2 (V-), U17.2 (GND), U18.2 (V-), U19.12 (GND), U20.1 (GND), U20.2 (GND), U20.3 (GND), U20.7 (GND), U21.1 (GND), U21.2 (GND), U21.3 (GND), U21.7 (GND), U22.8 (GND), U23.8 (GND), U24.8 (GND), U25.2 (GND), U26.2 (A1), U26.3 (A2), U26.12 (GND), U26.21 (A0), U27.2 (V-)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
GPIO_0: IC1.27 (IO0), SW1.1
HIDRV: Q4.4 (G), U11.15 (HIDRV)
JET_ON_FB: D11.1 (K), J5.1, R146.1
JET_PWR_BTN_CTRL: Q11.1 (G), R153.1, U43.17 (P14)
LODRV: Q6.4 (G), U11.13 (LODRV)
unnamed: C32.1, R15.2
unnamed: C43.1, R32.2
unnamed: C108.2, R162.1
unnamed: C109.2, R164.1
unnamed: D1.1 (A), D1.2 (A), L1.2, Q1.5 (D), Q1.6 (D), Q1.7 (D), Q1.8 (D)
unnamed: D2.1 (K), R12.1
unnamed: D3.1 (K), R13.1
unnamed: D6.1 (K), R31.1
unnamed: D7.2 (A), R30.2
unnamed: D7.1 (K), Q5.3 (D)
unnamed: D9.1 (K), R34.1
unnamed: D12.1 (K), R53.1
unnamed: D13.1 (K), R54.1
unnamed: D14.1 (K), J2.A5, R57.1
unnamed: D15.1 (K), J2.B5, R58.1
unnamed: D16.1 (K), R63.1
unnamed: D19.1 (K), J5.2, Q11.3 (D)
unnamed: D22.1 (K), R107.1
unnamed: D23.1 (K), R109.1
unnamed: D24.1 (K), R111.1
unnamed: D25.2 (A), U25.1
unnamed: D25.1 (K), R130.1
unnamed: D26.1 (K), R106.2, R122.1, U22.9 (IMON)
unnamed: D27.1 (K), R108.2, R124.1, U23.9 (IMON)
unnamed: D28.1 (K), R110.2, R127.1, U24.9 (IMON)
unnamed: D29.2 (A), U25.3
unnamed: D29.1 (K), R113.1
unnamed: D34.1 (K), R163.1
unnamed: D35.1 (K), R165.1
unnamed: D36.1 (K), R167.1
unnamed: D37.1 (K), R169.1
unnamed: D38.1 (K), R161.2, R177.1, U36.9 (IMON)
unnamed: D39.1 (K), R160.2, R180.1, U35.9 (IMON)
unnamed: D40.1 (K), R168.2, R181.1, U38.9 (IMON)
unnamed: D41.1 (K), R166.2, R187.1, U37.9 (IMON)
unnamed: C50.1, IC1.38 (IO2), U9.4
unnamed: IC1.19 (IO11), R44.2, R49.1
unnamed: JP1.1 (A), U8.11 (VDC_OUT)
unnamed: Q1.4 (G), U5.3 (GATE)
unnamed: Q1.1 (S), Q1.2 (S), Q1.3 (S), R4.1, R9.2
unnamed: Q2.3 (D), R12.2
unnamed: Q3.3 (D), R13.2
unnamed: Q7.3 (D), R31.2
unnamed: Q8.3 (D), R53.2
unnamed: Q9.3 (D), R54.2
unnamed: Q10.3 (D), R63.2
unnamed: Q12.3 (D), R107.2
unnamed: Q13.3 (D), R109.2
unnamed: Q14.3 (D), R111.2
unnamed: Q15.3 (D), R163.2
unnamed: Q16.3 (D), R165.2
unnamed: Q17.3 (D), R167.2
unnamed: Q18.3 (D), R169.2
unnamed: R11.2, R16.1, U3.6
unnamed: R26.1, R27.1, R28.1, U3.4
unnamed: R41.1, R45.1, U12.3
unnamed: R42.1, R46.1, U12.1
unnamed: R56.2, R59.1, U14.1
unnamed: R195.1, R196.2, R198.1
unnamed: R1.2, R6.1, U1.11 (EN)
unnamed: C24.1, R3.1, R5.1, U1.4 (FB)
unnamed: C26.2, U1.9 (VCC), U1.12 (MODE)
unnamed: C25.1, U1.5 (SS)
unnamed: C1.1, U1.8 (VBST)
unnamed: R2.1, R7.1, U4.3 (+)
unnamed: R14.1, R21.2, U4.4 (-)
unnamed: C31.1, R15.1, U5.6 (COMP)
unnamed: C27.1, R4.2, U5.5 (CS)
unnamed: R10.1, R20.1, U5.8 (FB)
unnamed: R17.2, U5.10 (RT)
unnamed: C30.1, U5.9 (SS)
unnamed: R22.1, R24.1, U6.4 (-)
unnamed: R23.1, R25.1, U7.4 (-)
unnamed: R29.1, U8.10 (FLIP)
unnamed: R21.1, U8.3 (VBUS_FET_EN)
unnamed: C33.1, U8.24 (VCCD)
unnamed: C56.1, R47.1, U11.4 (TS)
unnamed: C69.1, R51.1, R55.1, U13.4 (FB)
unnamed: C75.2, U13.9 (VCC), U13.12 (MODE)
unnamed: C74.1, U13.5 (SS)
unnamed: C62.1, U13.8 (VBST)
unnamed: R64.1, R67.1, U15.3 (+)
unnamed: R65.1, R68.1, U16.3 (+)
unnamed: C77.1, J2.A4-B9, J2.B4-A9, U17.5 (VBUS)
unnamed: R70.1, R71.1, U18.4 (-)
unnamed: R97.2, U19.10 (ILM)
unnamed: R74.2, R80.1, U19.5 (OV1)
unnamed: R89.2, R100.1, U19.4 (OV2)
unnamed: R72.2, R76.1, U19.6 (PR1)
unnamed: C93.2, U19.11 (SS)
unnamed: R120.1, U19.9 (ST), U30.3 (+)
unnamed: C95.2, U22.7 (DVDT)
unnamed: R86.1, R102.1, U22.2 (OVLO)
unnamed: R112.1, U22.3 (PG), U27.3 (+)
unnamed: R82.1, R91.1, U22.4 (PGTH)
unnamed: C98.2, U23.7 (DVDT)
unnamed: R83.1, R92.1, U23.1 (EN/UVLO)
unnamed: R92.2, R103.1, U23.2 (OVLO)
unnamed: R118.1, U23.3 (PG), U28.3 (+)
unnamed: R84.1, R93.1, U23.4 (PGTH)
unnamed: C99.2, U24.7 (DVDT)
unnamed: R85.1, R96.1, U24.2 (OVLO)
unnamed: R119.1, U24.3 (PG), U29.3 (+)
unnamed: R87.1, R94.1, U24.4 (PGTH)
unnamed: R81.1, R88.2, U26.4 (P00)
unnamed: R78.1, R90.2, U26.5 (P01)
unnamed: R75.1, R95.2, U26.6 (P02)
unnamed: R73.1, R98.2, U26.7 (P03)
unnamed: R99.2, R136.1, U26.8 (P04)
unnamed: R101.2, R132.1, U26.9 (P05)
unnamed: R104.2, R126.1, U26.10 (P06)
unnamed: R105.2, R121.1, U26.11 (P07)
unnamed: R123.1, R131.1, U27.4 (-)
unnamed: R125.1, R133.1, U28.4 (-)
unnamed: R128.1, R135.1, U29.4 (-)
unnamed: R129.1, R134.1, U30.4 (-)
unnamed: C106.2, U35.7 (DVDT)
unnamed: R142.1, R156.1, U35.2 (OVLO)
unnamed: R176.1, U35.3 (PG), U45.3 (+)
unnamed: R138.1, R147.1, U35.4 (PGTH)
unnamed: R162.2, U36.7 (DVDT)
unnamed: R143.1, R157.1, U36.2 (OVLO)
unnamed: R175.1, U36.3 (PG), U44.3 (+)
unnamed: R139.1, R148.1, U36.4 (PGTH)
unnamed: C107.2, U37.7 (DVDT)
unnamed: R144.1, R158.1, U37.2 (OVLO)
unnamed: R178.1, U37.3 (PG), U46.3 (+)
unnamed: R140.1, R149.2, U37.4 (PGTH)
unnamed: R164.2, U38.7 (DVDT)
unnamed: R145.1, R159.1, U38.2 (OVLO)
unnamed: R179.1, U38.3 (PG), U47.3 (+)
unnamed: R141.1, R150.1, U38.4 (PGTH)
unnamed: R146.2, R173.2, U43.4 (P00)
unnamed: R151.2, R172.2, U43.5 (P01)
unnamed: R152.2, R171.2, U43.6 (P02)
unnamed: R154.2, R170.2, U43.7 (P03)
unnamed: R155.2, R174.2, U43.8 (P04)
unnamed: R186.1, R191.1, U44.4 (-)
unnamed: R188.1, R192.1, U45.4 (-)
unnamed: R189.1, R193.1, U46.4 (-)
unnamed: R190.1, R194.1, U47.4 (-)
PD_INT: IC1.32 (IO39), R26.2, U8.7 (HPI_INT)
PD_SCL: IC1.34 (IO41), R28.2, U8.13 (HPI_SCL)
PD_SDA: IC1.33 (IO40), R27.2, U8.12 (HPI_SDA)
PG_DC: Q13.1 (G), R88.1, U28.1
PG_USB: Q12.1 (G), R95.1, U27.1
PMUX_ST: R44.1, U25.6, U30.1
RXD_0: D17.1 (K), IC1.36 (RXD0), J3.1
SCC_EN: R115.2, U11.2 (CE), U26.14 (P11)
SCC_ISET_SW: R116.2, U12.6, U26.15 (P12)
SCC_PG: Q8.1 (G), R98.1, U15.1
SCC_PG_N: R60.1, U11.5 (*PG), U15.4 (-)
SCC_PH: C48.2, L3.1, Q4.1 (S), Q4.2 (S), Q4.3 (S), Q6.5 (D), Q6.6 (D), Q6.7 (D), Q6.8 (D), U11.14 (PH)
SCC_STAT: Q9.1 (G), R99.1, U16.1
SCC_STAT_N: R61.1, U11.3 (STAT), U16.4 (-)
SCC_TS: R47.2, U14.4
SCC_TS_ADC: C57.1, IC1.39 (IO1), J4.1, R62.1, R69.2, U14.3
SCC_TS_SW: R117.2, U14.6, U26.16 (P13)
STAT_LED: IC1.4 (IO4), Q5.1 (G), R37.2
TXD_0: D18.1 (K), IC1.37 (TXD0), J3.2
USB_D+: IC1.14 (IO20), U17.4 (I/O2)
USB_D-: IC1.13 (IO19), U17.6 (I/O1)
VBUS_OUT: D30.3 (K), J7.1, R138.2, U35.6 (OUT), U39.4 (IN), U39.5 (IN), U39.6 (IN)
VBUS_USB_EN: R8.1, U4.1, U22.1 (EN/UVLO)
VCAP_ADC: R196.1, U9.1
VCAP_EN: IC1.35 (IO42), R38.1, U24.1 (EN/UVLO)
VCAP_PG: Q14.1 (G), R101.1, U29.1
VIMON_5V_SS: C49.1, IC1.12 (IO8), R168.1
VIMON_DC: C53.1, IC1.15 (IO3), R108.1
VIMON_EXT_5V_VBUS: C39.1, IC1.5 (IO5), R161.1
VIMON_EXT_SS: C46.1, IC1.7 (IO7), R166.1
VIMON_EXT_VBUS: C44.1, IC1.6 (IO6), R160.1
VIMON_SC: C61.1, IC1.18 (IO10), R110.1
VIMON_USB: C58.1, IC1.17 (IO9), R106.1

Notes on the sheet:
20V->5V SS BUCK
IN1 = +VBUS (PRIMARY) | IN2 = +VCAP_VALID (ARMED BACKUP) VALID INPUT RANGE: 2.8-22.8 V | CURRENT LIMIT: ≈4.55 A TYP HANDOVER: VBUS→VCAP @17.6 V↓ | VCAP→VBUS @17.7 V↑ | ≈5 µs TYP
OVLO_R=7.0V, OVLO_F=6.5V PGTH_R=4.5V, PGTH_F=4.1V T_CH=84ms, I_CH=0.23A (@COUT = 4000uF)
DC INRUSH CTRL
V_OUT = 2.1x(1+RFT/RFB) = 20.6V
12V<=VIN<=21V, VOUT=3V3, IOUT_MAX=100mA
3V3 VCAP LDO
SUPER CAP SWITCH
24.5V BOOST
USB-C->ESP32 (NO PWR)
ESP32 LEDs
3V3 VBUS LDO
BOOT + RESET
OVLO_R=22.8V, OVLO_F=20.9V PGTH_R=17.1V, PGTH_F=15.65V T_CH=47ms, I_CH=0.2A (@COUT = 480uF)
3V3 SS LDO
SS POWER SWITCH
VBUS POWER SWITCH
POWER MUX
20V->5V BUCK
I2C -> GPIO INTERNAL CONTROL
I_CHARGE = V_ISET / (20 x R_SR), SCC_ISET_SW LOW -> I_CHARGE=1A, SCC_ISET_SW HIGH -> I_CHARGE=1.9A
5V SS POWER SWITCH
VCAP ADC DIV
OVLO_R=22.8V, OVLO_F=20.9V PGTH_R=4.5V, PGTH_F=4.1V T_CH=47ms, I_CH=0.2A (@COUT = 480uF)
9V<=V_IN<=20.5V, V_OUT = 5.1V, I_OUT_MAX = 5A
VIN=5V, VOUT=3V3, IOUT_MAX=1A
VBUS_MIN,VBUS_MAX = 3V3 -> 20V FROM USBC
UVLO_R=17.5V, UVLO_F=16.0V, OVLO_R=22.1V, OVLO_F=20.3V PGTH_R=17.1V, PGTH_F=15.65V T_CH=47ms, I_CH=0.2A (@COUT = 480uF)
I2C -> GPIO EXTERNAL CONTROL
OVLO_R=7.0V, OVLO_F=6.5V PGTH_R=4.5V, PGTH_F=4.11V T_CH=84ms, I_CH=0.23A (@COUT = 4000uF)
2V5 VCAP VREF
OVLO_R=22.8V, OVLO_F=20.9V PGTH_R=9.9V, PGTH_F=9.1V T_CH=47ms, I_CH=0.2A (@COUT = 480uF)
5V VBUS POWER SWITCH
12V<=VIN<=21V, VOUT=24.5V, IOUT_MAX=2A
SOFT START = 16.8ms, I_INRUSH BASED ON C_LOAD OF 2000u IS 0.6A
A2:A0 = 000 → 7-BIT I²C ADDRESS 0x20
ESP32 UART0
ESP32-S3
ISINK IS NOT GUARANTEED, ANY ADVERTISED CURRENT IS ACCEPTED, READ BY ESP32 TO VALIDATE
USBC PD
